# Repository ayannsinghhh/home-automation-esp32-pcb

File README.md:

# home-automation-esp32-pcb
# 🏠 ESP32-Based Home Automation PCB

## 📌 Overview

This project is a custom-designed **home automation PCB** built using an ESP32, aimed at controlling multiple household appliances through relay switching.

Instead of using off-the-shelf relay modules, the system is designed from scratch at the circuit level — including relay driving, power conversion, and proper interfacing.

---

## ⚙️ System Architecture

The PCB integrates three main sections:

### 🔌 Power Supply

* AC input (Live & Neutral)
* Fuse protection (250mA)
* AC-DC conversion using HLK-PM01 module
* Regulated +5V output for the system

### 🧠 Controller Unit

* ESP32 DevKit (main controller)
* GPIO pins used to control relay drivers
* I2C interface for sensors (future expansion)

### ⚡ Relay Driver Section

Each appliance is controlled through an independent relay circuit:

* BC547 transistor used as a switch
* 1N4007 diode for flyback protection
* LED indicators for relay status
* 5V relay modules (G5LE-1 type)

This ensures:

* Safe switching of high-voltage loads
* Protection of ESP32 from back EMF

---

## 🔌 Output Connections

* Screw terminals provided for REL1 to REL5 (appliance outputs)
* Separate Live connections for each relay
* Designed for practical home wiring

---

## 📡 Expandability

* I2C header (SDA, SCL) for future sensors
* DHT sensor interface
* Modular approach for adding IoT features (Blynk/MQTT)

---

## 🧠 Design Understanding

This PCB was designed with a focus on:

* Proper separation of low voltage (ESP32) and high voltage (AC load)
* Reliable relay switching using transistor drivers
* Clean and scalable architecture for future upgrades

---

## ⚠️ Safety Considerations

* Fuse added for input protection
* Flyback diodes across relay coils
* Care required while handling AC mains

---

## 🛠️ Tools Used

* KiCad for schematic and PCB design
* ESP32 for control logic

---

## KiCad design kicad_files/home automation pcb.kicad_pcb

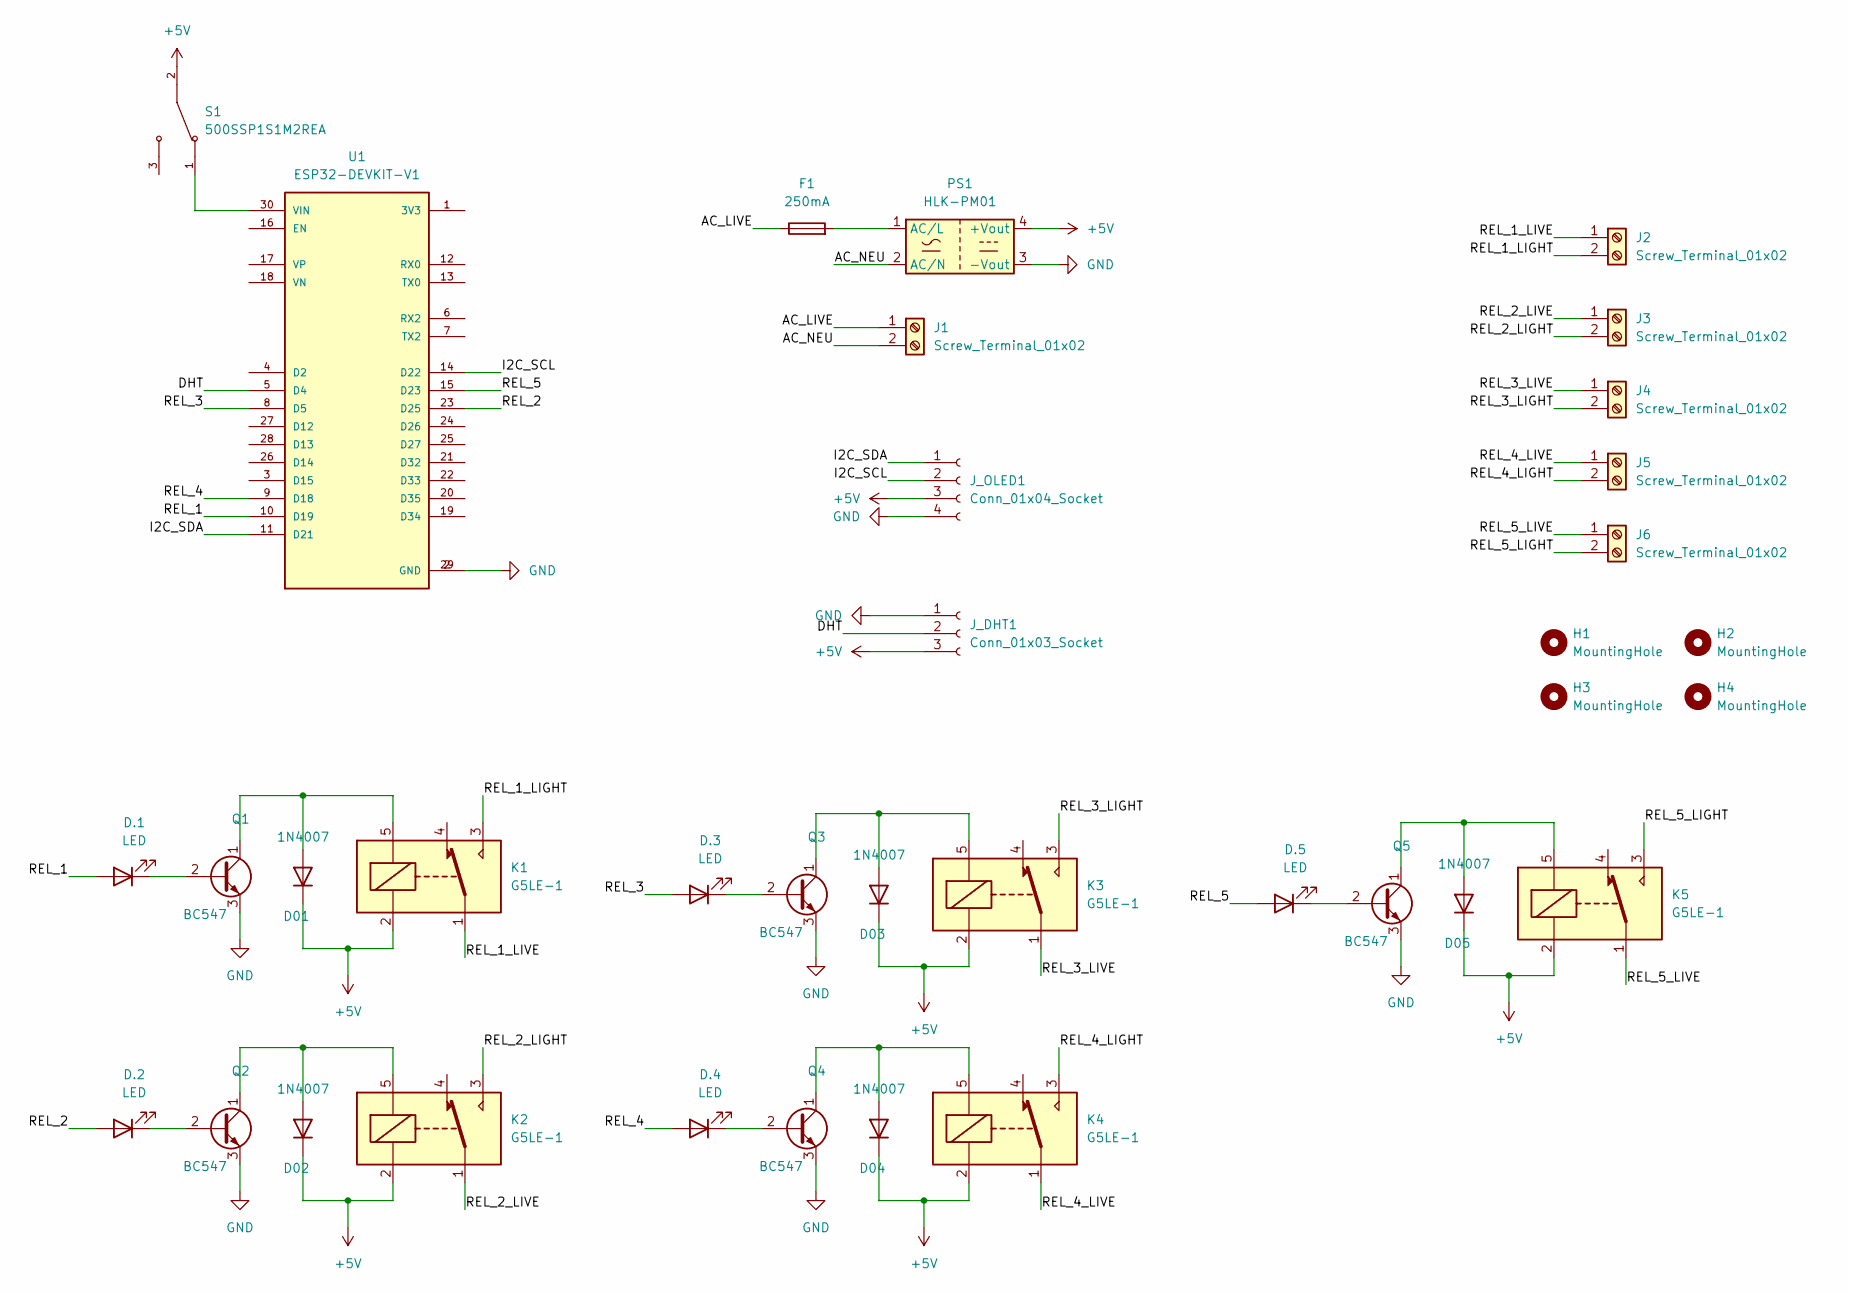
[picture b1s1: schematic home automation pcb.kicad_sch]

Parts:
D01, D02, D03, D04, D05: 1N4007; D_DO-41_SOD81_P10.16mm_Horizontal
D.1, D.2, D.3, D.4, D.5: LED; LED_0805_2012Metric_Pad1.15x1.40mm_HandSolder
F1: 250mA; Fuseholder_Cylinder-5x20mm_Wuerth_696103101002-SMD_Horizont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
H1, H2, H3, H4: MountingHole; MountingHole_2.1mm
J1, J2, J3, J4, J5, J6: Screw_Terminal_01x02; TerminalBlock_Phoenix_MKDS-1,5-2-5.08_1x02_P5.08mm_Horizont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
J_DHT1: Conn_01x03_Socket; PinSocket_1x03_P2.54mm_Vertical
J_OLED1: Conn_01x04_Socket; PinSocket_1x04_P2.54mm_Vertical
K1, K2, K3, K4, K5: G5LE-1; Relay_SPDT_Omron-G5LE-1
PS1: HLK-PM01; Converter_ACDC_Hi-Link_HLK-PMxx
Q1, Q2, Q3, Q4, Q5: BC547; TO-92_Inline
S1: 500SSP1S1M2REA; SW_500SSP1S1M2REA
U1: ESP32-DEVKIT-V1; MODULE_ESP32_DEVKIT_V1; PARTREV N/A

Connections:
+5V: D01.1 (K), D02.1 (K), D03.1 (K), D04.1 (K), D05.1 (K), J_DHT1.3, J_OLED1.3, K1.2, K2.2, K3.2, K4.2, K5.2, PS1.4 (+Vout), S1.2
/AC_LIVE: F1.1, J1.1
/AC_NEU: J1.2, PS1.2 (AC/N)
/DHT: J_DHT1.2, U1.5 (D4)
/I2C_SCL: J_OLED1.2, U1.14 (D22)
/I2C_SDA: J_OLED1.1, U1.11 (D21)
/REL_1: D.1.2 (A), U1.10 (D19)
/REL_1_LIGHT: J2.2, K1.3
/REL_1_LIVE: J2.1, K1.1
/REL_2: D.2.2 (A), U1.23 (D25)
/REL_2_LIGHT: J3.2, K2.3
/REL_2_LIVE: J3.1, K2.1
/REL_3: D.3.2 (A), U1.8 (D5)
/REL_3_LIGHT: J4.2, K3.3
/REL_3_LIVE: J4.1, K3.1
/REL_4: D.4.2 (A), U1.9 (D18)
/REL_4_LIGHT: J5.2, K4.3
/REL_4_LIVE: J5.1, K4.1
/REL_5: D.5.2 (A), U1.15 (D23)
/REL_5_LIGHT: J6.2, K5.3
/REL_5_LIVE: J6.1, K5.1
GND: J_DHT1.1, J_OLED1.4, PS1.3 (-Vout), Q1.3 (E), Q2.3 (E), Q3.3 (E), Q4.3 (E), Q5.3 (E), U1.2 (GND), U1.29 (GND)
unnamed: D01.2 (A), K1.5, Q1.1 (C)
unnamed: D02.2 (A), K2.5, Q2.1 (C)
unnamed: D03.2 (A), K3.5, Q3.1 (C)
unnamed: D04.2 (A), K4.5, Q4.1 (C)
unnamed: D05.2 (A), K5.5, Q5.1 (C)
unnamed: D.1.1 (K), Q1.2 (B)
unnamed: D.2.1 (K), Q2.2 (B)
unnamed: D.3.1 (K), Q3.2 (B)
unnamed: D.4.1 (K), Q4.2 (B)
unnamed: D.5.1 (K), Q5.2 (B)
unnamed: F1.2, PS1.1 (AC/L)
unnamed: S1.1, U1.30 (VIN)

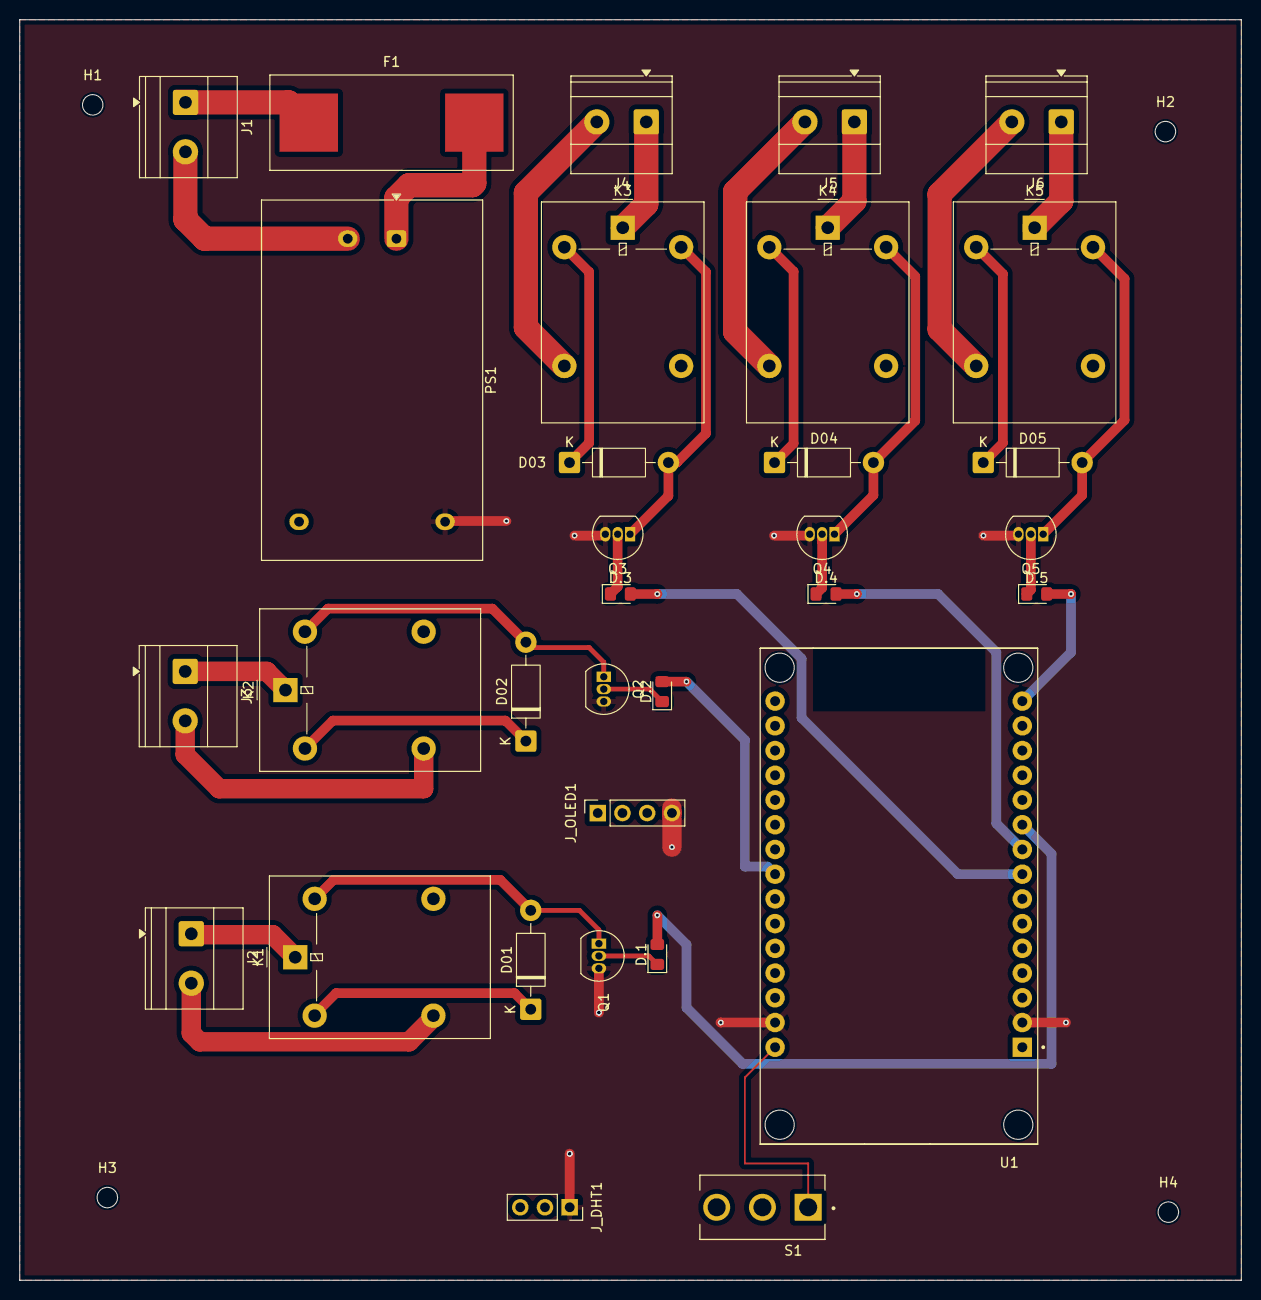
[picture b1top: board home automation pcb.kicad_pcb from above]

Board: 2 copper layers, 125.5 x 129.5 mm, 36 parts (0 on the bottom side), 34 nets.

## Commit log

2026-04-25 Create images
2026-04-25 Create image
2026-04-25 Create file
